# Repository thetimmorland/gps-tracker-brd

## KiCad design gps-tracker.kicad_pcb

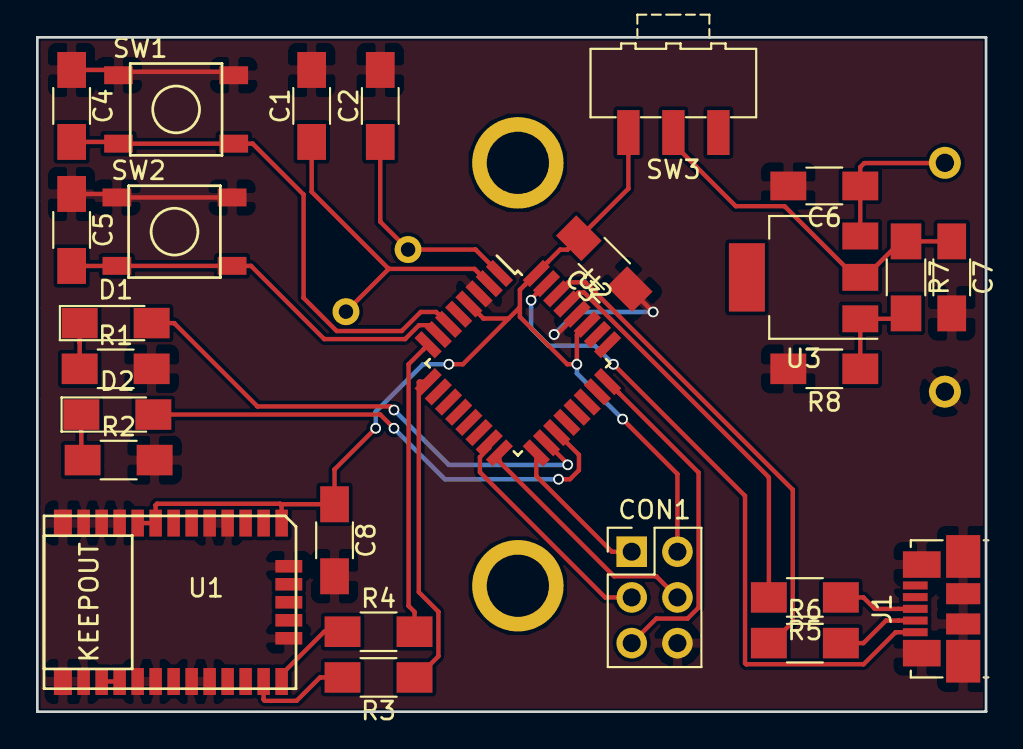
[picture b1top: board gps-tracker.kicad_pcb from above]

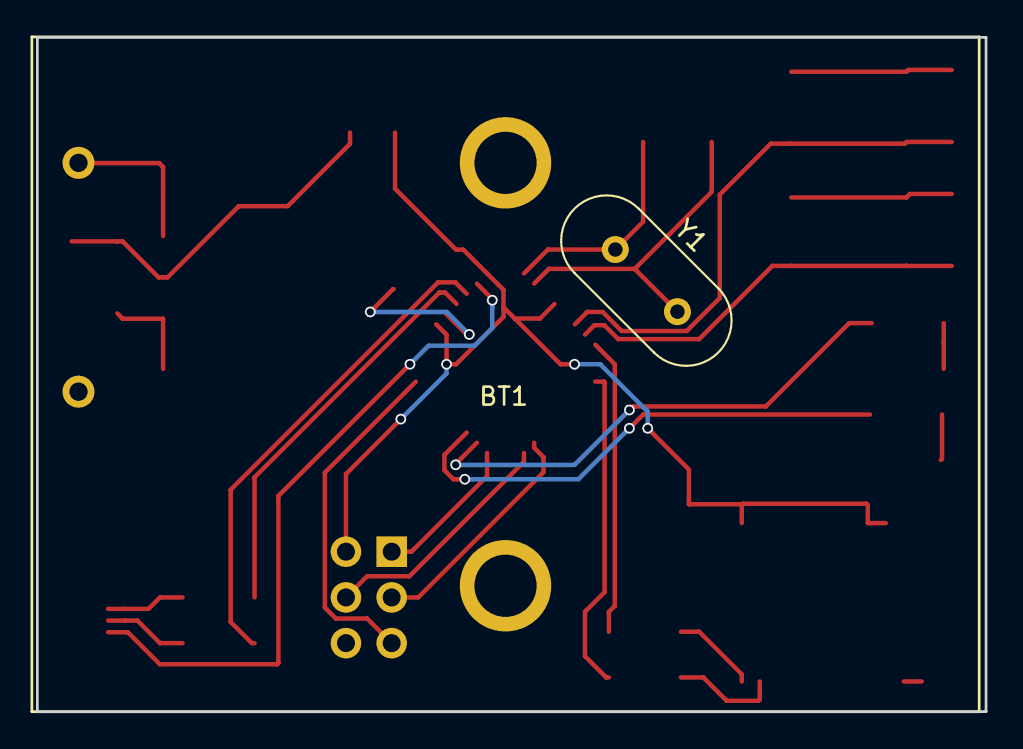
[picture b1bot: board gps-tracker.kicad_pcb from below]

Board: 2 copper layers, 52.7 x 37.5 mm, 28 parts (2 on the bottom side), 27 nets.

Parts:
BT1: Primary; 2479-AAA-Battery
C1, C2: 22pF; C_1206_HandSoldering
C3, C4, C5, C6, C7: 1uF; C_1206_HandSoldering
C8: 4.7uF; C_1206_HandSoldering
CON1: AVR-ISP-6; Pin_Header_Straight_2x03_Pitch2.54mm
D1, D2: LED_Small; LED_1206_HandSoldering
J1: USB_OTG; USB_Micro-B_Molex_47346-0001
R1, R2: 100; R_1206_HandSoldering
R3, R4: 220; R_1206_HandSoldering
R5, R6: 22; R_1206_HandSoldering
R7, R8: 330; R_1206_HandSoldering
SW1, SW2: SW_Push_Dual; PTS525_SM15
SW3: PWR; SW_SPDT_CK-JS102011SAQN
U1: CAM-M8
U2: ATMEGA16U2-AU; TQFP-32_7x7mm_Pitch0.8mm
U3: 3.3 LDO; SOT-223
Y1: 16MHz; Crystal_HC49-U_Vertical

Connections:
+3V3: C3.2, C8.1, CON1.2, SW3.3, U1.1, U1.8, U1.9, U2.4, U2.27, U2.32
/MISO: CON1.1, U2.17
/MOSI: CON1.4, U2.16
/RST: CON1.5, U2.24
/RXD: R4.2, U2.8
/SCK: CON1.3, U2.15
/TXD: R3.1, U2.9
GND: BT1.2, C1.2, C2.2, C3.1, C4.1, C5.1, C6.2, C7.2, C8.2, CON1.6, J1.5, J1.6, R1.2, R2.2, R8.2, SW1.2, SW1.4, SW2.2, SW2.4, U1.4, U1.5, U1.10, U1.11, U1.12, U1.13, U1.14, U1.15, U1.18, U1.19, U1.21, U1.22, U1.27, U1.31, U2.3, U2.28
unnamed: BT1.1, C6.1, U3.3
unnamed: C1.1, U2.2, Y1.2
unnamed: C2.1, U2.1, Y1.1
unnamed: C4.2, SW1.1, SW1.3, U2.6
unnamed: C5.2, SW2.1, SW2.3, U2.7
unnamed: C7.1, R7.1, SW3.2, U3.2
unnamed: D1.1, R1.1
unnamed: D1.2, U2.18
unnamed: D2.1, R2.1
unnamed: D2.2, U2.19
unnamed: J1.1, U2.31
unnamed: J1.2, R6.2
unnamed: J1.3, R5.1
unnamed: R3.2, U1.25
unnamed: R4.1, U1.26
unnamed: R5.2, U2.29
unnamed: R6.1, U2.30
unnamed: R7.2, R8.1, U3.1
unnamed: U1.16, U1.17

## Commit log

2018-05-27 first order
